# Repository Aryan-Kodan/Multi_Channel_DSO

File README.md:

# Multi-Channel Digital Storage Oscilloscope (DSO)

A custom **Multi-Channel Digital Storage Oscilloscope (DSO)** designed using the **STM32F103C8T6** microcontroller. This project combines a custom analog front-end, trigger circuitry, anti-alias filtering, multi-channel acquisition architecture, and a TFT display into a compact oscilloscope platform.

The analog signal conditioning was designed and verified in **LTspice**, while the complete hardware was developed in **KiCad**, including schematic capture, PCB layout, and 3D visualization.

---

# Features

- Multi-channel analog acquisition architecture
- Custom analog front-end
- Input over-voltage protection
- Adjustable gain stage
- DC offset stage
- Hardware trigger comparator
- RC anti-alias filter
- STM32F103 ADC interface
- TFT display interface
- SWD programming and debugging
- Two-layer PCB
- LTspice verified analog stages

---

# Hardware Specifications

| Parameter | Specification |
|-----------|---------------|
| MCU | STM32F103C8T6 |
| ADC | 12-bit Internal ADC |
| Channels | Multi-Channel Architecture |
| Input Protection | TVS + Schottky Clamp |
| Trigger | Hardware Comparator |
| Anti-Alias Filter | RC Low Pass |
| Display | EA_eDIPTFT32-A TFT |
| Interface | I²C |
| PCB | 2-Layer |

---

# Repository Structure

```
Multi-Channel-DSO/
│
├── BOM/
│   └── DSO.xlsx
│
├── images/
│   ├── KiCad/
│   │   ├── PCB.png
│   │   ├── PCB_3D.png
│   │   ├── PCB_3D_through.png
│   │   ├── Schematic.png
│   ├── LTspice/
│   │   ├── Final_output.png
│   │   ├── Input_waveform.png
│   │   ├── Gain_waveform.png
│   │   ├── offset_waveform.png
│   │   └── Spice_Schematic.png
│
├── KiCad/
│   ├── DSO.kicad_pro
│   ├── DSO.kicad_sch
│   └── DSO.kicad_pcb
│
├── LTspice/
│   └── Osc_front.asc
│
└── README.md
```

---

# System Architecture

```
                Analog Input
                     │
                     ▼
             Input Protection
          (TVS + Clamp Diodes)
                     │
                     ▼
             Buffer Amplifier
                     │
                     ▼
           Programmable Gain Stage
                     │
                     ▼
              DC Offset Stage
                     │
                     ▼
           Trigger Comparator
                     │
                     ├────────► STM32 Trigger Input
                     │
                     ▼
            RC Anti-Alias Filter
                     │
                     ▼
              STM32 ADC + DMA
                     │
                     ▼
            Waveform Processing
                     │
                     ▼
                TFT Display
```

---

# Analog Signal Chain

The complete analog front-end consists of:

- Input protection
- Voltage scaling
- Buffer amplifier
- Gain amplifier
- DC offset stage
- Trigger comparator
- RC anti-alias filter
- ADC interface

The design conditions incoming analog signals into the STM32 ADC input range while maintaining waveform integrity.

---

# LTspice Simulation

The complete analog signal chain was verified before PCB implementation.

Simulation stages include:

- Input waveform
- Gain stage response
- Offset stage response
- Final conditioned output
- Complete analog schematic

---

# PCB Design

The PCB was designed using **KiCad** with emphasis on:

- Compact component placement
- Analog and digital section separation
- Ground plane implementation
- Short analog signal routing
- Decoupling capacitor placement
- SWD programming interface
- TFT display interface

---

# Development Workflow

- Analog front-end design
- LTspice verification
- Schematic capture
- PCB layout
- 3D PCB visualization
- BOM generation
- Embedded firmware development *(in progress)*
- Hardware validation *(planned)*

---

# Software Used

- KiCad 9
- LTspice
- Git
- GitHub

---

# Future Improvements

- Dual simultaneous ADC acquisition
- External high-speed ADC
- DMA circular buffer implementation
- Auto trigger mode
- Single-shot trigger
- FFT spectrum analyzer
- USB waveform streaming
- SD card waveform storage
- Automatic measurements
- Cursor functions
- Frequency and duty-cycle measurement
- Rotary encoder user interface

---

# Author

**Aryan Kodan**

Electronics Engineering | Embedded Systems | PCB Design | Analog Circuit Design | VLSI

GitHub: https://github.com/Aryan-Kodan

---

# License

This project is released under the MIT License.

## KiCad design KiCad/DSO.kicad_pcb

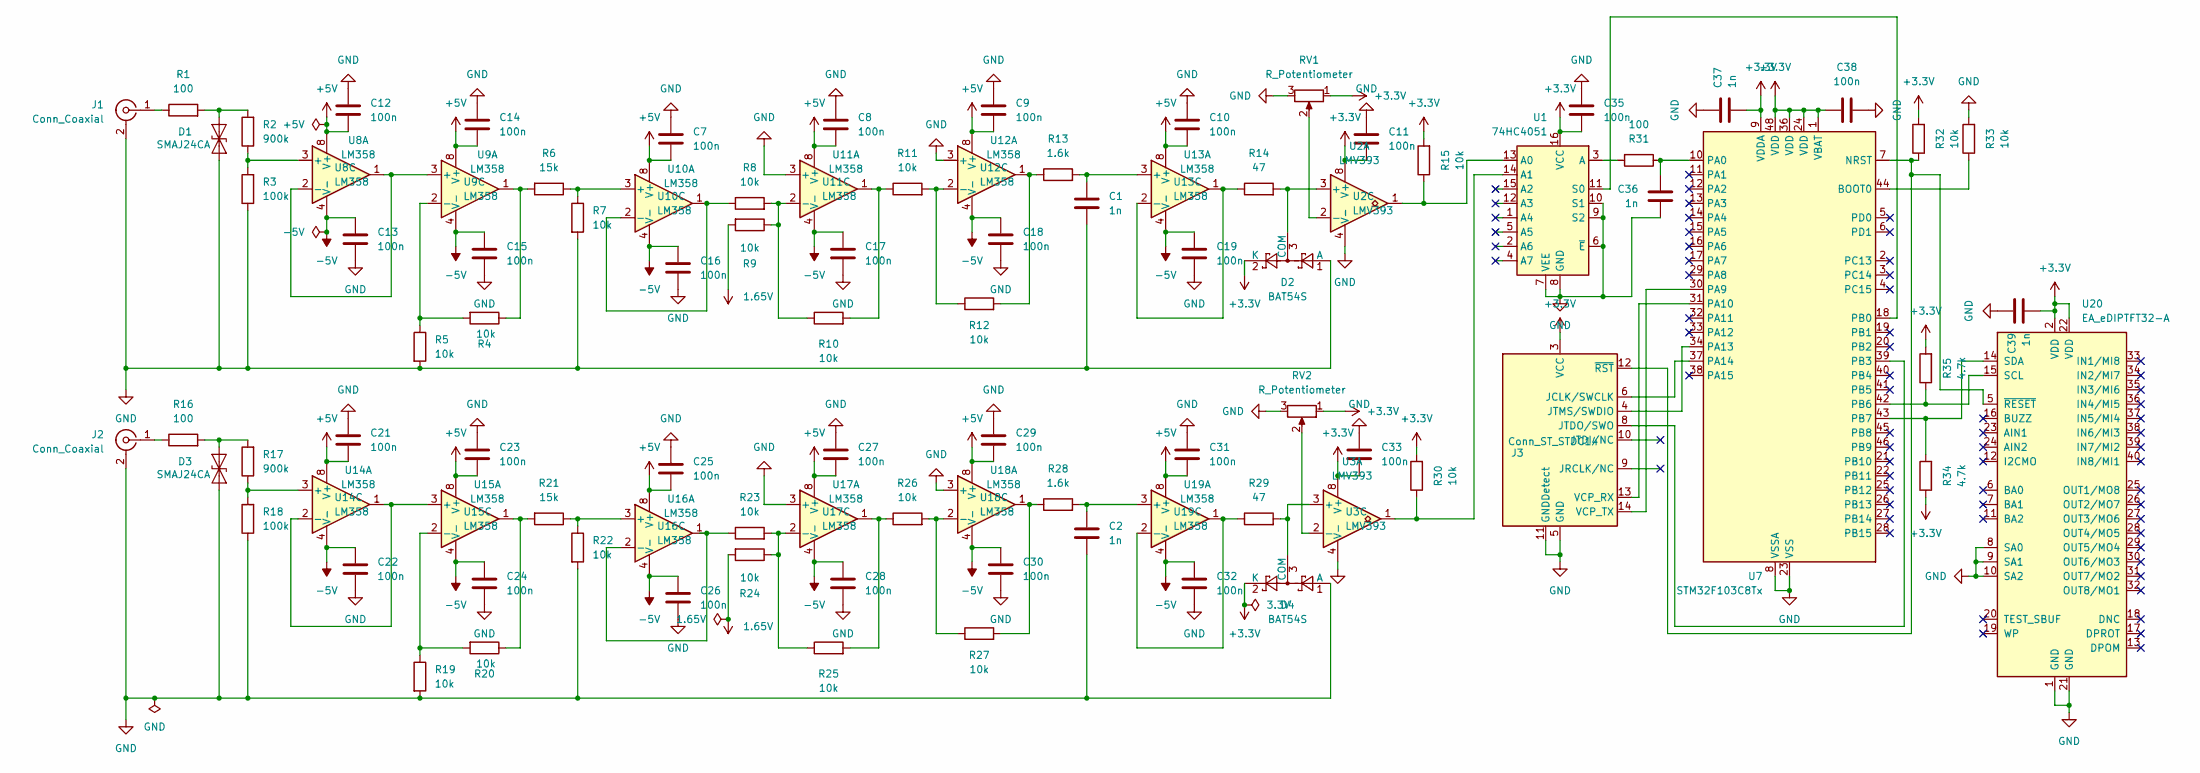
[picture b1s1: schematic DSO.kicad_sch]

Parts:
C1, C2, C36, C37, C39: 1n; C_0805_2012Metric
C7, C8, C9, C10, C11, C12, C13, C14, C15, C16, C17, C18, C19, C21, C22, C23, C24, C25, C26, C27, C28, C29, C30, C31, C32, C33, C35, C38: 100n; C_0805_2012Metric
D1, D3: SMAJ24CA; D_SMA
D2, D4: BAT54S; SOT-23
J1, J2: Conn_Coaxial; BNC_Amphenol_031-6575_Horizontal
J3: Conn_ST_STDC14; PinHeader_2x07_P1.27mm_Vertical
R1, R16, R31: 100; R_0805_2012Metric
R2, R17: 900k; R_0805_2012Metric
R3, R18: 100k; R_0805_2012Metric
R4, R5, R7, R8, R9, R10, R11, R12, R15, R19, R20, R22, R23, R24, R25, R26, R27, R30, R32, R33: 10k; R_0805_2012Metric
R6, R21: 15k; R_0805_2012Metric
R13, R28: 1.6k; R_0805_2012Metric
R14, R29: 47; R_0805_2012Metric
R34, R35: 4.7k; R_0805_2012Metric
RV1, RV2: R_Potentiometer; Potentiometer_Bourns_3214W_Vertical
U1: 74HC4051; TSSOP-16-1EP_4.4x5mm_P0.65mm
U2, U3: LMV393; SOIC-8_3.9x4.9mm_P1.27mm
U7: STM32F103C8Tx; LQFP-48_7x7mm_P0.5mm
U8, U9, U10, U11, U12, U13, U14, U15, U16, U17, U18, U19: LM358; SOIC-8_3.9x4.9mm_P1.27mm
U20: EA_eDIPTFT32-A; EA_eDIPTFT32-XXX

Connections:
1.65V: R9.2, R24.2
+3.3V: C11.2, C33.2, C35.2, C37.2, C38.2, C39.2, D2.2 (K), D4.2 (K), J3.3 (VCC), R15.2, R30.2, R32.2, R34.1, R35.2, RV1.1, RV2.1, U1.16 (VCC), U2.8 (V+), U3.8 (V+), U7.1 (VBAT), U7.9 (VDDA), U7.24 (VDD), U7.36 (VDD), U7.48 (VDD), U20.2 (VDD), U20.22 (VDD)
+5V: C7.2, C8.2, C9.2, C10.2, C12.2, C14.2, C21.2, C23.2, C25.2, C27.2, C29.2, C31.2, U8.8 (V+), U9.8 (V+), U10.8 (V+), U11.8 (V+), U12.8 (V+), U13.8 (V+), U14.8 (V+), U15.8 (V+), U16.8 (V+), U17.8 (V+), U18.8 (V+), U19.8 (V+)
-5V: C13.1, C15.1, C16.1, C17.1, C18.1, C19.1, C22.1, C24.1, C26.1, C28.1, C30.1, C32.1, U8.4 (V-), U9.4 (V-), U10.4 (V-), U11.4 (V-), U12.4 (V-), U13.4 (V-), U14.4 (V-), U15.4 (V-), U16.4 (V-), U17.4 (V-), U18.4 (V-), U19.4 (V-)
GND: C1.2, C2.2, C7.1, C8.1, C9.1, C10.1, C11.1, C12.1, C13.2, C14.1, C15.2, C16.2, C17.2, C18.2, C19.2, C21.1, C22.2, C23.1, C24.2, C25.1, C26.2, C27.1, C28.2, C29.1, C30.2, C31.1, C32.2, C33.1, C35.1, C36.2, C37.1, C38.1, C39.1, D1.1 (A1), D2.1 (A), D3.1 (A1), D4.1 (A), J1.2 (Ext), J2.2 (Ext), J3.5 (GND), J3.7 (GND), J3.11 (GNDDetect), R3.1, R5.2, R7.2, R18.1, R19.2, R22.2, R33.2, RV1.3, RV2.3, U1.6 (~E), U1.7 (VEE), U1.8 (GND), U1.9 (S2), U1.10 (S1), U2.4 (V-), U3.4 (V-), U7.8 (VSSA), U7.23 (VSS), U7.35 (VSS), U7.47 (VSS), U11.3 (+), U12.3 (+), U17.3 (+), U18.3 (+), U20.1 (GND), U20.8 (SA0), U20.9 (SA1), U20.10 (SA2), U20.21 (GND)
unnamed: D1.2 (A2), R1.2, R2.2
unnamed: D2.3 (COM), R14.2, U2.3 (+)
unnamed: D3.2 (A2), R16.2, R17.2
unnamed: D4.3 (COM), R29.2, U3.3 (+)
unnamed: J1.1 (In), R1.1
unnamed: J2.1 (In), R16.1
unnamed: J3.6 (JCLK/SWCLK), U7.37 (PA14)
unnamed: J3.8 (JTDO/SWO), U7.39 (PB3)
unnamed: J3.4 (JTMS/SWDIO), U7.34 (PA13)
unnamed: J3.13 (VCP_RX), U7.31 (PA10)
unnamed: J3.14 (VCP_TX), U7.30 (PA9)
unnamed: J3.12 (~RST), R32.1, U7.7 (NRST), U20.5 (~RESET)
unnamed: R4.1, R6.2, U9.1
unnamed: R10.2, R11.1, U11.1
unnamed: R12.2, R13.1, U12.1
unnamed: R20.1, R21.2, U15.1
unnamed: R25.2, R26.1, U17.1
unnamed: R27.2, R28.1, U18.1
unnamed: R15.1, U1.13 (A0), U2.1
unnamed: R30.1, U1.14 (A1), U3.1
unnamed: R31.2, U1.3 (A)
unnamed: U1.11 (S0), U7.18 (PB0)
unnamed: RV1.2, U2.2 (-)
unnamed: RV2.2, U3.2 (-)
unnamed: R33.1, U7.44 (BOOT0)
unnamed: C36.1, R31.1, U7.10 (PA0)
unnamed: R2.1, R3.2, U8.3 (+)
unnamed: U8.1, U8.2 (-), U9.3 (+)
unnamed: R4.2, R5.1, U9.2 (-)
unnamed: R6.1, R7.1, U10.3 (+)
unnamed: R8.1, U10.1, U10.2 (-)
unnamed: R8.2, R9.1, R10.1, U11.2 (-)
unnamed: R11.2, R12.1, U12.2 (-)
unnamed: C1.1, R13.2, U13.3 (+)
unnamed: R14.1, U13.1, U13.2 (-)
unnamed: R17.1, R18.2, U14.3 (+)
unnamed: U14.1, U14.2 (-), U15.3 (+)
unnamed: R19.1, R20.2, U15.2 (-)
unnamed: R21.1, R22.1, U16.3 (+)
unnamed: R23.1, U16.1, U16.2 (-)
unnamed: R23.2, R24.1, R25.1, U17.2 (-)
unnamed: R26.2, R27.1, U18.2 (-)
unnamed: C2.1, R28.2, U19.3 (+)
unnamed: R29.1, U19.1, U19.2 (-)
unnamed: R35.1, U7.42 (PB6), U20.15 (SCL)
unnamed: R34.2, U7.43 (PB7), U20.14 (SDA)

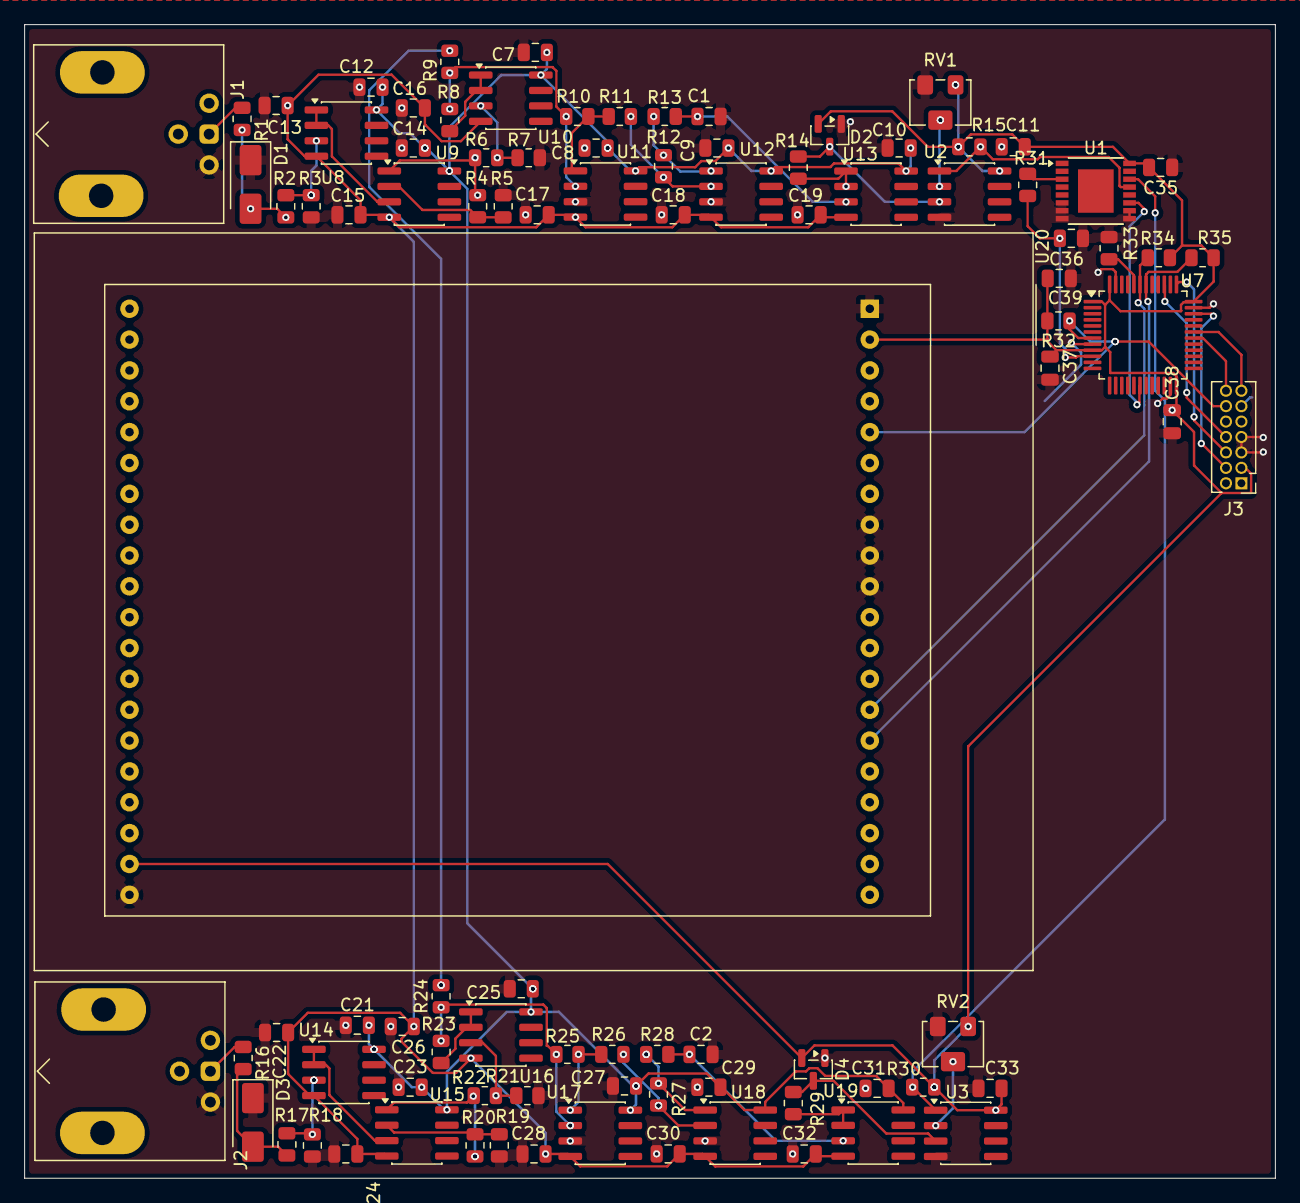
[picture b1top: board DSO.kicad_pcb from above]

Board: 2 copper layers, 103.0 x 95.0 mm, 94 parts (0 on the bottom side), 51 nets.
